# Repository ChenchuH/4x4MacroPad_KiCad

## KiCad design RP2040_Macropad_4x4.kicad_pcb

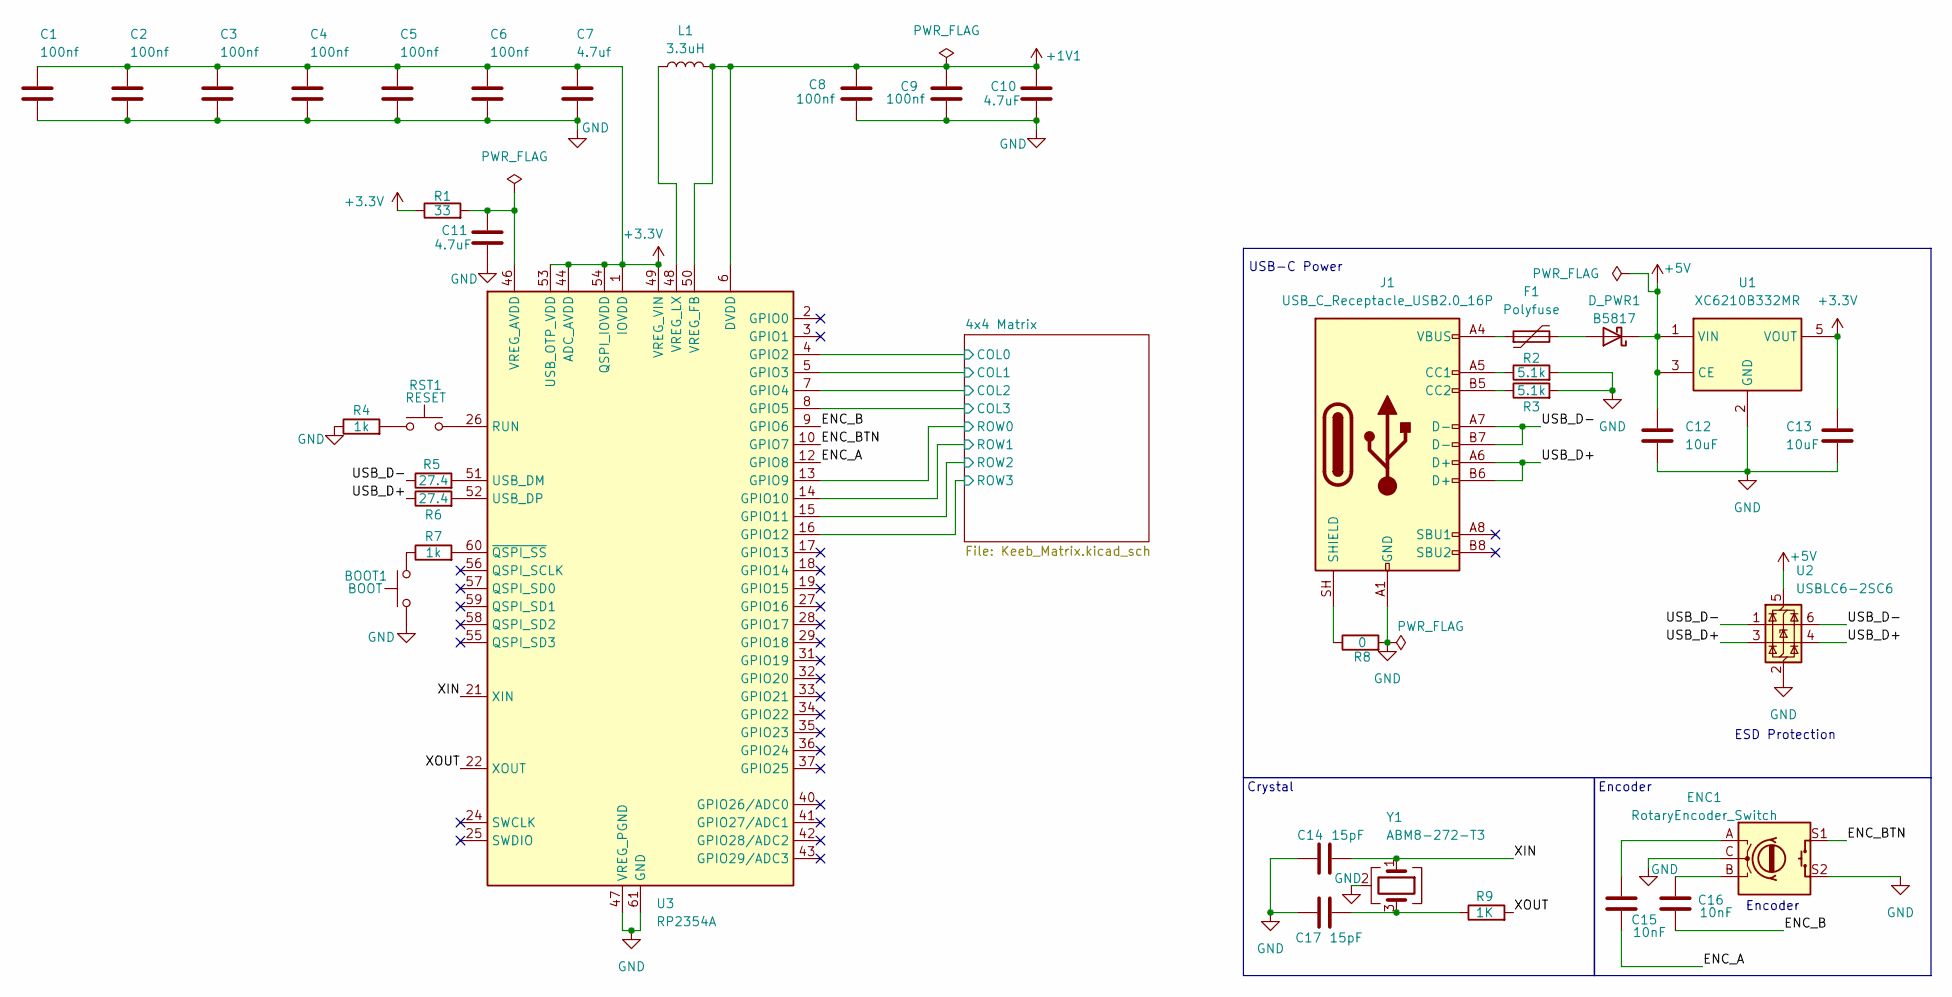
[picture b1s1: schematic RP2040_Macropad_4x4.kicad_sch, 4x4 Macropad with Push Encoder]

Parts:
BOOT1: BOOT; SW_SPST_B3U-1000P
C1, C2, C3, C4, C5, C6, C8, C9: 100nf; C_0402_1005Metric
C7: 4.7uf; C_0402_1005Metric
C10, C11: 4.7uF; C_0402_1005Metric
C12, C13: 10uF; C_0603_1608Metric
C14, C17: 15pF; C_0603_1608Metric
C15, C16: 10nF; C_0402_1005Metric
D_PWR1: B5817; D_SOD-123
ENC1: RotaryEncoder_Switch; RotaryEncoder_Bourns_Vertical_PEC12R-3x17F-Sxxxx
F1: Polyfuse; Fuse_0805_2012Metric
J1: USB_C_Receptacle_USB2.0_16P; USB_C_Receptacle_HRO_TYPE-C-31-M-12
L1: 3.3uH; L_0805_2012Metric
R1: 33; R_0402_1005Metric
R2, R3: 5.1k; R_0603_1608Metric
R4, R7: 1k; R_0603_1608Metric
R5, R6: 27.4; R_0402_1005Metric
R8: 0; R_0603_1608Metric
R9: 1K; R_0402_1005Metric
RST1: RESET; SW_SPST_B3U-1000P
U1: XC6210B332MR; SOT-23-5
U2: USBLC6-2SC6; SOT-23-6
U3: RP2354A; QFN-60-1EP_7x7mm_P0.4mm_EP3.4x3.4mm
Y1: ABM8-272-T3; Crystal_SMD_3225-4Pin_3.2x2.5mm

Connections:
+1V1: C8.1, C9.1, C10.1, L1.2, U3.6 (DVDD), U3.23 (DVDD), U3.39 (DVDD), U3.50 (VREG_FB)
+3.3V: C1.1, C2.1, C3.1, C4.1, C5.1, C6.1, C7.1, C13.1, R1.1, U1.5 (VOUT), U3.1 (IOVDD), U3.11 (IOVDD), U3.20 (IOVDD), U3.30 (IOVDD), U3.38 (IOVDD), U3.44 (ADC_AVDD), U3.45 (IOVDD), U3.49 (VREG_VIN), U3.53 (USB_OTP_VDD), U3.54 (QSPI_IOVDD)
+5V: C12.1, D_PWR1.1 (K), U1.1 (VIN), U1.3 (CE), U2.5 (VBUS)
/4x4 Matrix/COL0: U3.4 (GPIO2); also elsewhere on the board
/4x4 Matrix/COL1: U3.5 (GPIO3); also elsewhere on the board
/4x4 Matrix/COL2: U3.7 (GPIO4); also elsewhere on the board
/4x4 Matrix/COL3: U3.8 (GPIO5); also elsewhere on the board
/4x4 Matrix/ROW0: U3.13 (GPIO9); also elsewhere on the board
/4x4 Matrix/ROW1: U3.14 (GPIO10); also elsewhere on the board
/4x4 Matrix/ROW2: U3.15 (GPIO11); also elsewhere on the board
/4x4 Matrix/ROW3: U3.16 (GPIO12); also elsewhere on the board
/ENC_A: C15.2, U3.12 (GPIO8)
/ENC_B: C16.2, U3.9 (GPIO6)
/ENC_BTN: ENC1.S1, U3.10 (GPIO7)
/USB_D+: J1.A6 (D+), J1.B6 (D+), R6.1, U2.3 (I/O2), U2.4 (I/O2)
/USB_D-: J1.A7 (D-), J1.B7 (D-), R5.1, U2.1 (I/O1), U2.6 (I/O1)
/XIN: C14.2, U3.21 (XIN), Y1.1
/XOUT: R9.2, U3.22 (XOUT)
GND: BOOT1.1, C1.2, C2.2, C3.2, C4.2, C5.2, C6.2, C7.2, C8.2, C9.2, C10.2, C11.2, C12.2, C13.2, C14.1, C17.1, ENC1.C, ENC1.S2, J1.A1 (GND), J1.A12 (GND), J1.B1 (GND), J1.B12 (GND), R2.2, R3.2, R4.1, R8.2, U1.2 (GND), U2.2 (GND), U3.47 (VREG_PGND), U3.61 (GND), Y1.2 (G), Y1.4 (G)
unnamed: BOOT1.2, R7.1
unnamed: C15.1, ENC1.A
unnamed: C16.1, ENC1.B
unnamed: C17.2, R9.1, Y1.3
unnamed: D_PWR1.2 (A), F1.2
unnamed: F1.1, J1.A4 (VBUS), J1.A9 (VBUS), J1.B4 (VBUS), J1.B9 (VBUS)
unnamed: J1.A5 (CC1), R2.1
unnamed: J1.B5 (CC2), R3.1
unnamed: J1.SH (SHIELD), R8.1
unnamed: R4.2, RST1.1
unnamed: RST1.2, U3.26 (RUN)
unnamed: R5.2, U3.51 (USB_DM)
unnamed: R6.2, U3.52 (USB_DP)
unnamed: C11.1, R1.2, U3.46 (VREG_AVDD)
unnamed: L1.1, U3.48 (VREG_LX)
unnamed: R7.2, U3.60 (~QSPI_SS)

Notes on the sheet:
Encoder
USB-C Power
Encoder
ESD Protection
Crystal

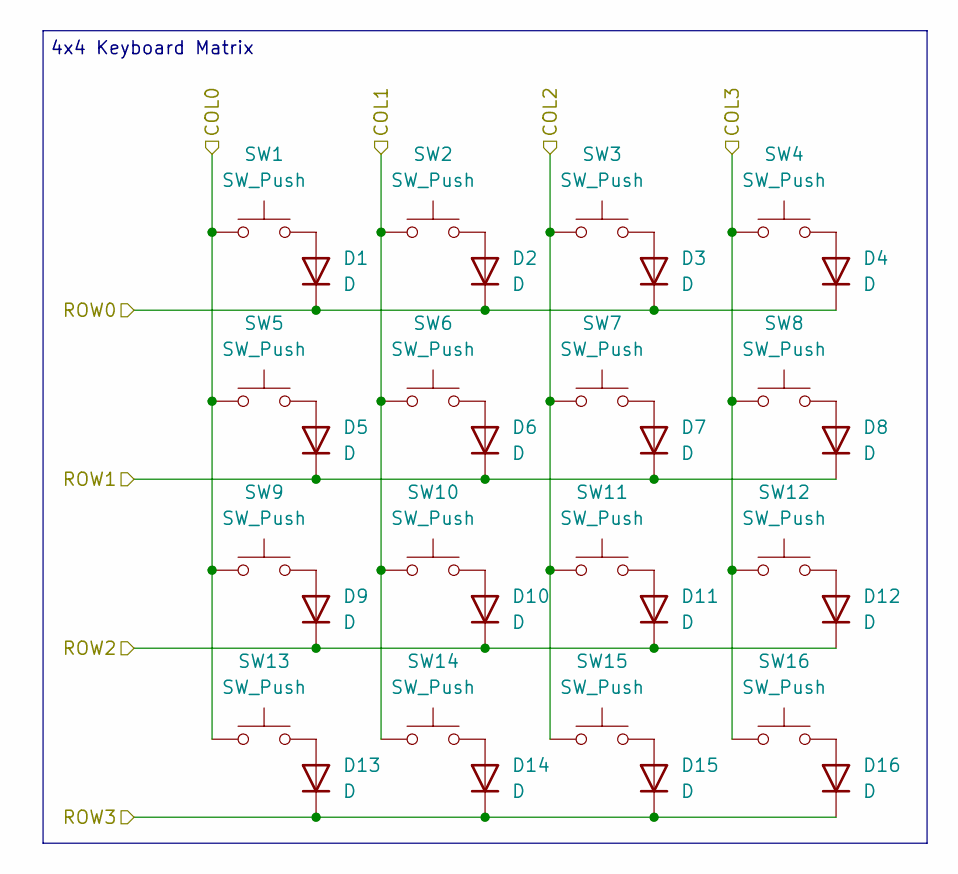
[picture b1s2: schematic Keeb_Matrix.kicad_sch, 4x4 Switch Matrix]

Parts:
D1, D2, D3, D4, D5, D6, D7, D8, D9, D10, D11, D12, D13, D14, D15, D16: D; D_SOD-323
SW1, SW2, SW3, SW4, SW5, SW6, SW7, SW8, SW9, SW10, SW11, SW12, SW13, SW14, SW15, SW16: SW_Push; SW_Cherry_MX_1.00u_PCB_Custom

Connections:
/4x4 Matrix/COL0: SW1.1, SW5.1, SW9.1, SW13.1; also elsewhere on the board
/4x4 Matrix/COL1: SW2.1, SW6.1, SW10.1, SW14.1; also elsewhere on the board
/4x4 Matrix/COL2: SW3.1, SW7.1, SW11.1, SW15.1; also elsewhere on the board
/4x4 Matrix/COL3: SW4.1, SW8.1, SW12.1, SW16.1; also elsewhere on the board
/4x4 Matrix/ROW0: D1.1 (K), D2.1 (K), D3.1 (K), D4.1 (K); also elsewhere on the board
/4x4 Matrix/ROW1: D5.1 (K), D6.1 (K), D7.1 (K), D8.1 (K); also elsewhere on the board
/4x4 Matrix/ROW2: D9.1 (K), D10.1 (K), D11.1 (K), D12.1 (K); also elsewhere on the board
/4x4 Matrix/ROW3: D13.1 (K), D14.1 (K), D15.1 (K), D16.1 (K); also elsewhere on the board
unnamed: D1.2 (A), SW1.2
unnamed: D2.2 (A), SW2.2
unnamed: D3.2 (A), SW3.2
unnamed: D4.2 (A), SW4.2
unnamed: D5.2 (A), SW5.2
unnamed: D6.2 (A), SW6.2
unnamed: D7.2 (A), SW7.2
unnamed: D8.2 (A), SW8.2
unnamed: D9.2 (A), SW9.2
unnamed: D10.2 (A), SW10.2
unnamed: D11.2 (A), SW11.2
unnamed: D12.2 (A), SW12.2
unnamed: D13.2 (A), SW13.2
unnamed: D14.2 (A), SW14.2
unnamed: D15.2 (A), SW15.2
unnamed: D16.2 (A), SW16.2

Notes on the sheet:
4x4 Keyboard Matrix

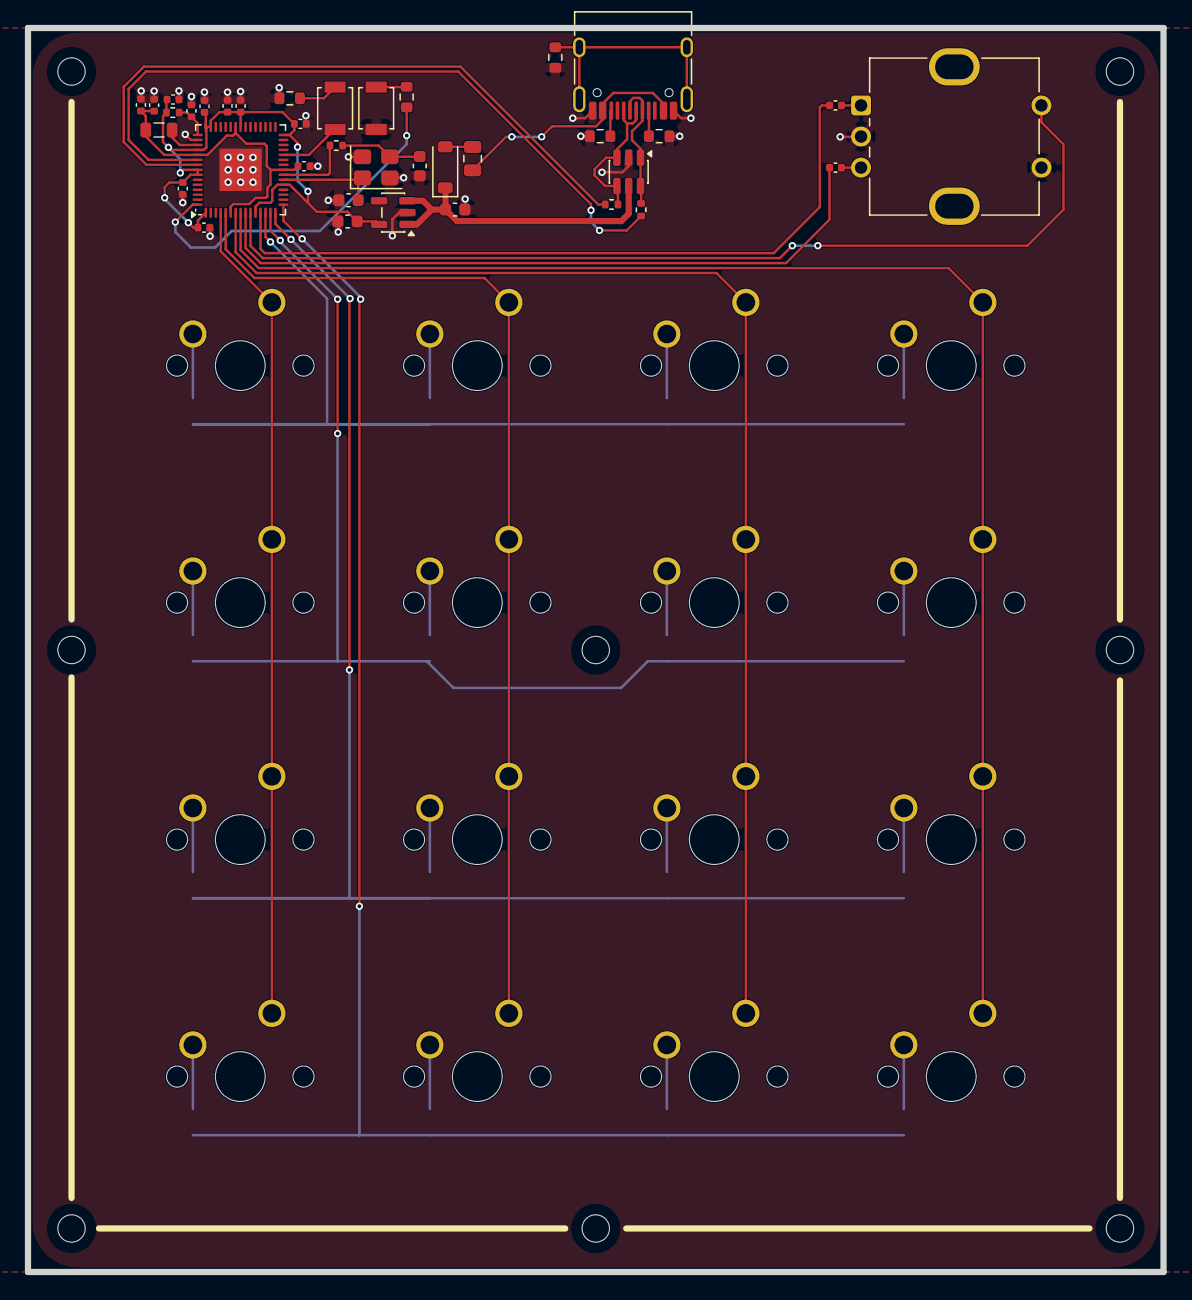
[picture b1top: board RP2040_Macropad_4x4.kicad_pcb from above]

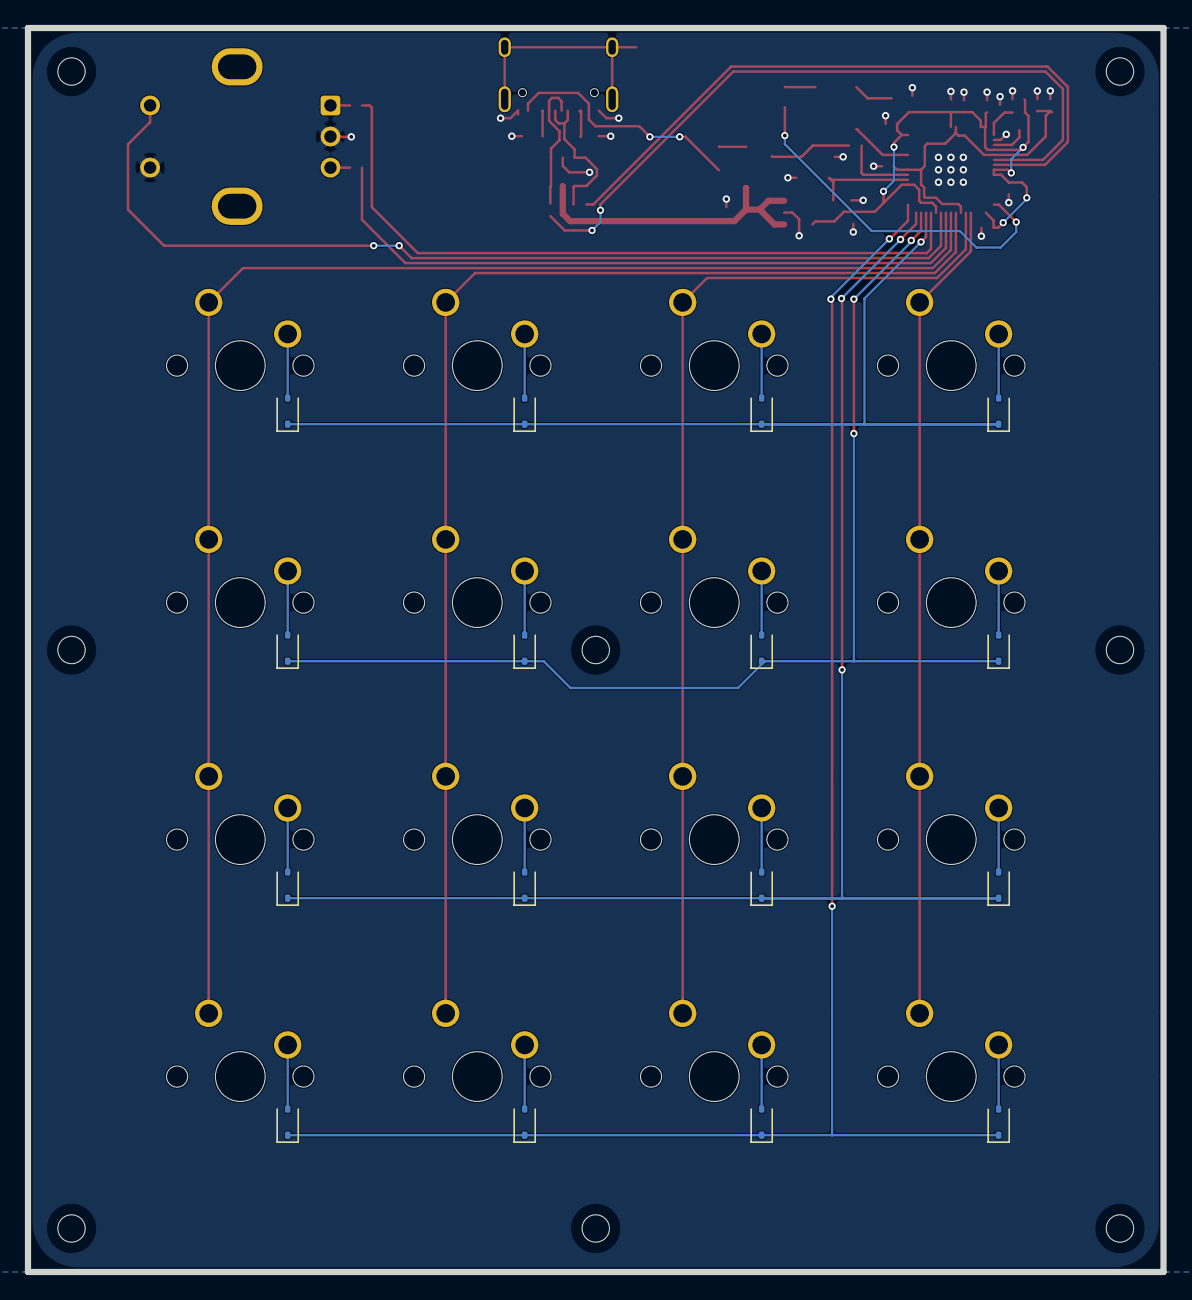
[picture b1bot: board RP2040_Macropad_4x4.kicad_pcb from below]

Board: 2 copper layers, 91.3 x 100.0 mm, 69 parts (16 on the bottom side), 51 nets.
